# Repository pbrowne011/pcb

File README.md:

# pcb

This is a collection of schematics and PCB designs using KiCad. Each directory
contains one or more project directories, where each project has an associated
schematic and (possibly) a PCB design file.

## Schematics
Some schematics I've designed so far:

<div align=center>
    
    <p>Arduino UNO and right-shift register with 8 LEDs</p>
    
    <p>Simple LED schematic</p>
</div>

## PCB Designs
Some PCB designs I've created so far:
    
<div align=center>
    
    <p>Arduino UNO and right-shift register with 8 LEDs</p>
    
    <p>Simple LED PCB</p>
</div>

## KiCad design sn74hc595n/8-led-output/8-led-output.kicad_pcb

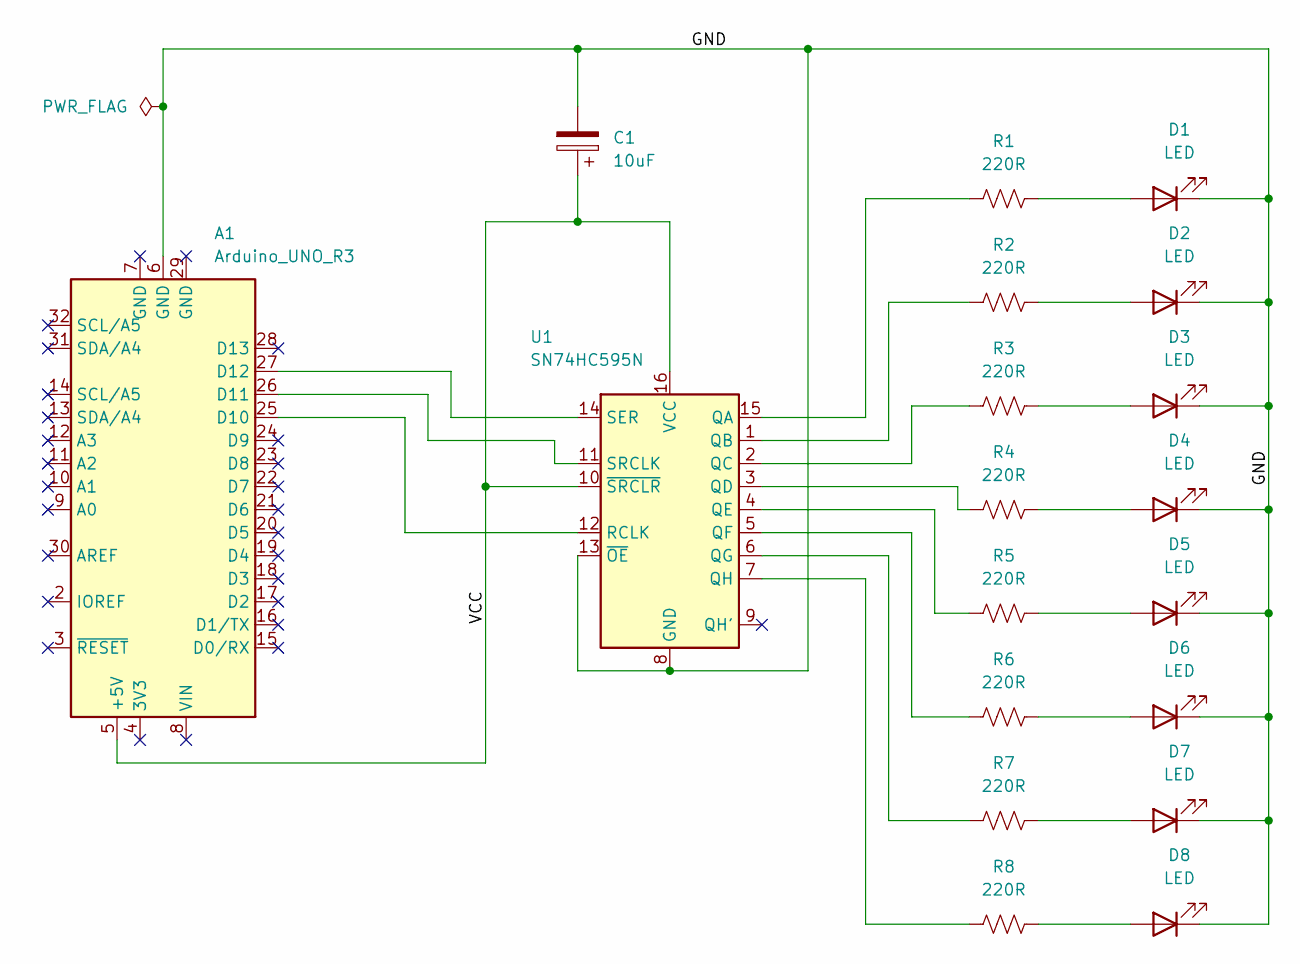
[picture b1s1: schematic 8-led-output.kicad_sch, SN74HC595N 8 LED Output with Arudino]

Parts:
A1: Arduino_UNO_R3
C1: 10uF; CP_Radial_D5.0mm_P2.50mm
D1, D2, D3, D4, D5, D6, D7, D8: LED; LED_D5.0mm
R1, R2, R3, R4, R5, R6, R7, R8: 220R; R_Axial_DIN0207_L6.3mm_D2.5mm_P10.16mm_Horizontal
U1: SN74HC595N; DIP-16_W7.62mm_LongPads

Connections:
/GND: A1.6 (GND), C1.2, D1.1 (K), D2.1 (K), D3.1 (K), D4.1 (K), D5.1 (K), D6.1 (K), D7.1 (K), D8.1 (K), U1.8 (GND), U1.13 (~OE)
/VCC: A1.5 (+5V), C1.1, U1.10 (~SRCLR), U1.16 (VCC)
unnamed: A1.25 (D10), U1.12 (RCLK)
unnamed: A1.26 (D11), U1.11 (SRCLK)
unnamed: A1.27 (D12), U1.14 (SER)
unnamed: D1.2 (A), R1.2
unnamed: D2.2 (A), R2.2
unnamed: D3.2 (A), R3.2
unnamed: D4.2 (A), R4.2
unnamed: D5.2 (A), R5.2
unnamed: D6.2 (A), R6.2
unnamed: D7.2 (A), R7.2
unnamed: D8.2 (A), R8.2
unnamed: R1.1, U1.15 (QA)
unnamed: R2.1, U1.1 (QB)
unnamed: R3.1, U1.2 (QC)
unnamed: R4.1, U1.3 (QD)
unnamed: R5.1, U1.4 (QE)
unnamed: R6.1, U1.5 (QF)
unnamed: R7.1, U1.6 (QG)
unnamed: R8.1, U1.7 (QH)

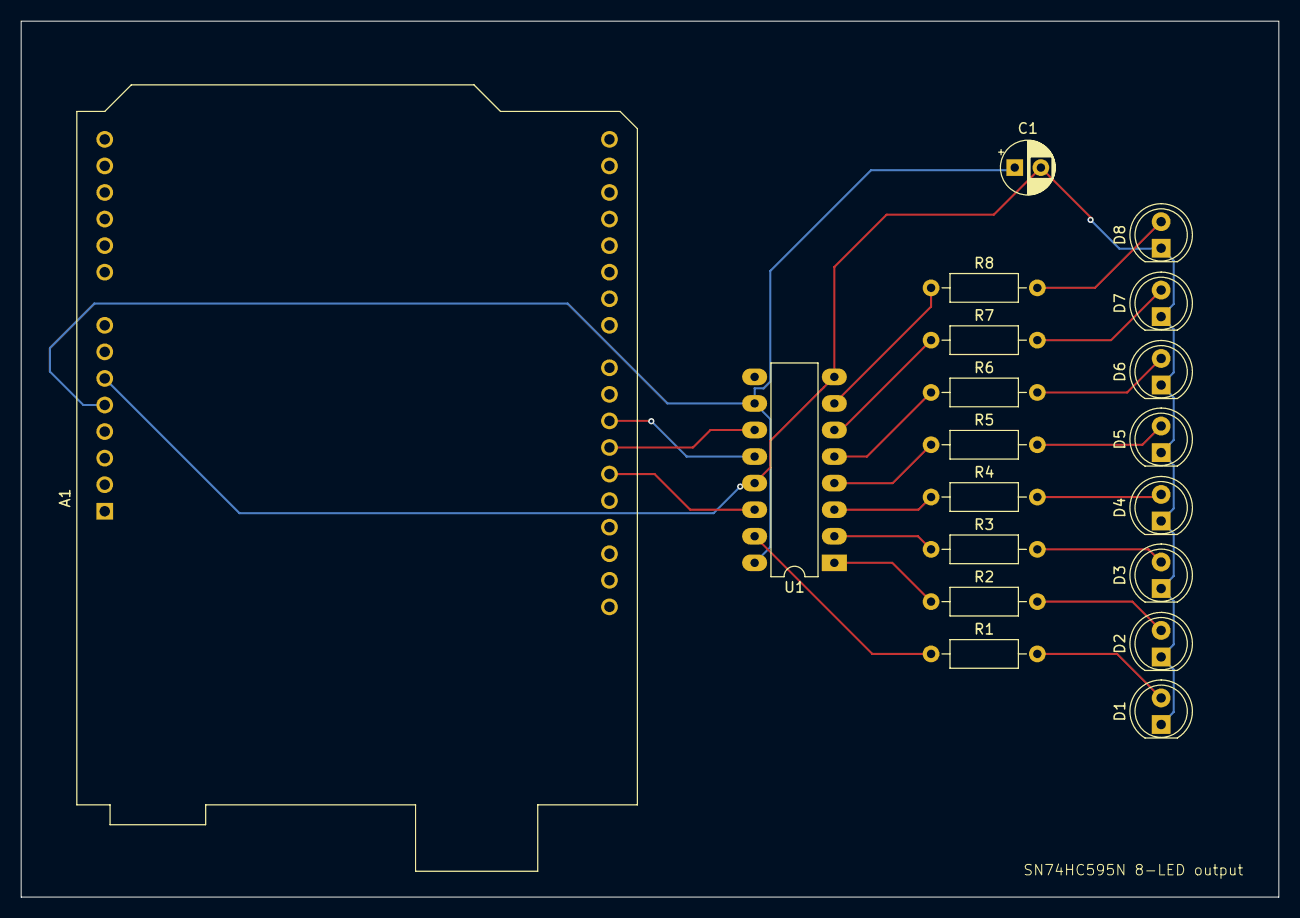
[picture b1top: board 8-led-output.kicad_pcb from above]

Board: 2 copper layers, 120.2 x 83.8 mm, 19 parts (0 on the bottom side), 21 nets.

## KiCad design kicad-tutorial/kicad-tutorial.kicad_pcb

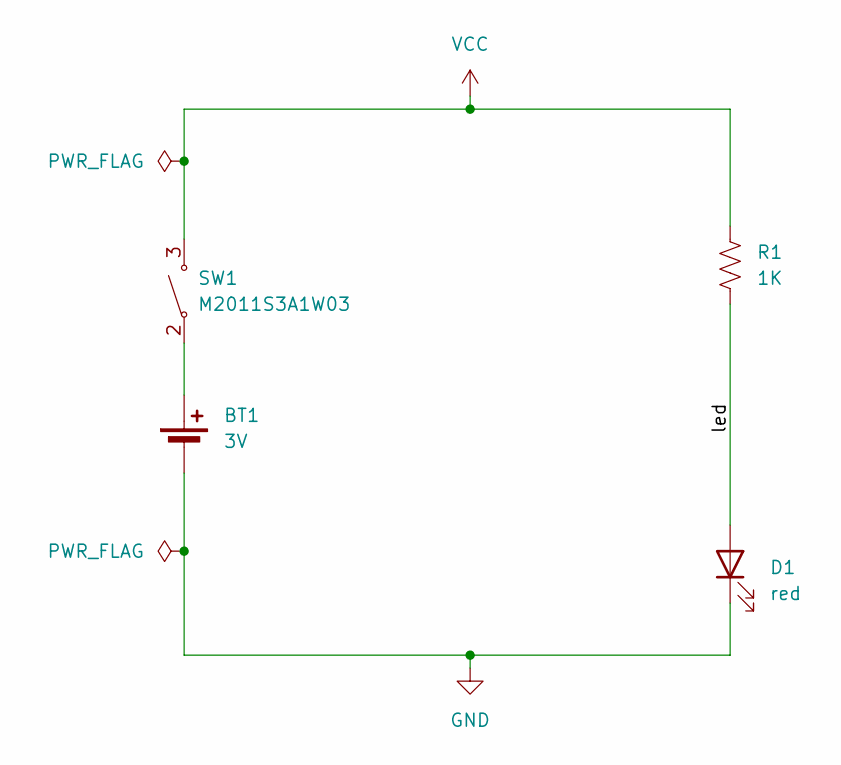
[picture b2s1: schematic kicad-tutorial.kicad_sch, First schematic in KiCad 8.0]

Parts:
BT1: 3V; BatteryHolder_Keystone_1058_1x2032
D1: red; LED_D5.0mm
R1: 1K; R_Axial_DIN0309_L9.0mm_D3.2mm_P12.70mm_Horizontal
SW1: M2011S3A1W03; Switch_Toggle_SPST_NKK_M2011S3A1x03

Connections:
/led: D1.2 (A), R1.2
GND: BT1.2 (-), D1.1 (K)
unnamed: BT1.1 (+), SW1.2 (A)
VCC: R1.1, SW1.3 (A)

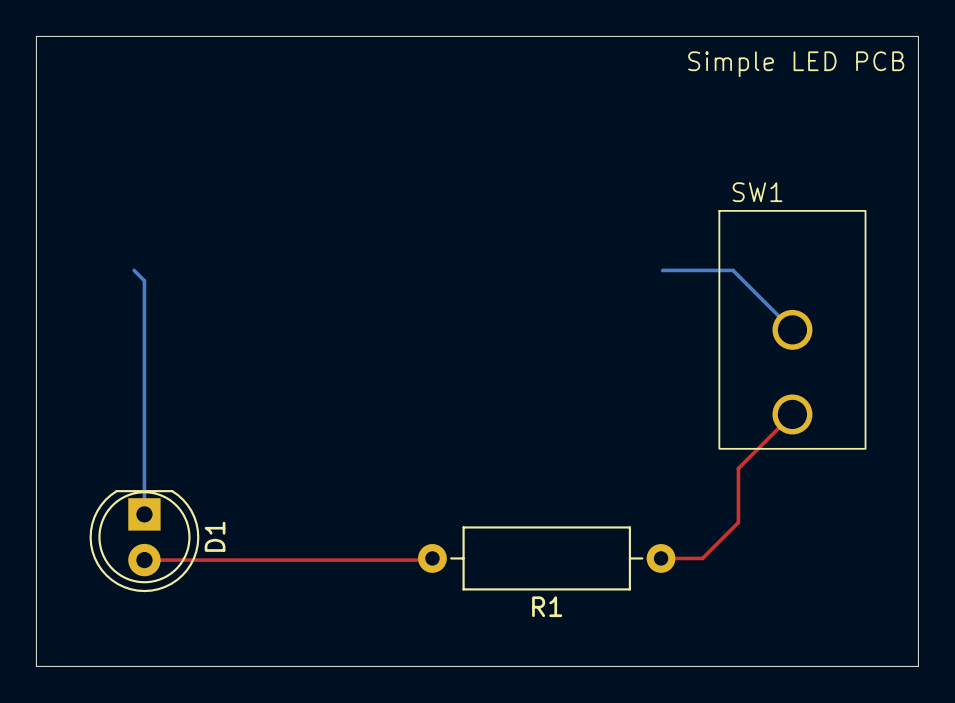
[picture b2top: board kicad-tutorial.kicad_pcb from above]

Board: 2 copper layers, 49.0 x 35.0 mm, 4 parts (1 on the bottom side), 4 nets.

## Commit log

2024-10-15 add first pcb
2024-10-15 add first project
2024-10-15 fix img width
2024-10-15 add switch to kicad-tutorial
2024-10-15 add new simple-led img, .gitignore
2024-10-15 remove backup file
2024-10-16 update .gitignore, remove files
    Adds more KiCad files to be ignored from version control (and public
    GitHub).
2024-10-16 add sn74ch595n/8-led-output
2024-10-16 update README.md formatting
